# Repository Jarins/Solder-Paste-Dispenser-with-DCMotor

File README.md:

# 3D Printed Solder-Paste-Dispenser with DC motor
Motorized automatic solder paste dispenser. Easily printable on a 3D printer at home
+ **Thanks [kevarek](https://hackaday.io/Kevarek) for inspiration from this [project:](https://hackaday.io/project/169748-low-cost-solder-paste-dispenser)**
+ The idea came from this project, including some parts of the source code that were partially or completely reworked and many new ones added. 

## __Work-in-progress__ Latest version 2.21.11.3010

### Some differences:

+ Controled with 32bit processor STM32F103C8T6 ( original is STM32F030)
+ used output H-bridge for motor control [TB67H451FNG](https://www.aliexpress.com/item/1005001738294266.html?spm=a2g0s.9042311.0.0.27424c4dVMVyey). **No need cooling with during operation**.
+ 

+ [DC micromotor 6V / 60 rpm](https://www.aliexpress.com/item/33022320164.html?spm=a2g0s.9042311.0.0.266b4c4dmW3uVV) with gearbox without thread rod 

+ [Coupler](https://www.aliexpress.com/item/1005002015620915.html?spm=a2g0s.9042311.0.0.266b4c4dmW3uVV) 3/4mm to thread rod M4.

+ larger [syringe 10 ccm](https://www.aliexpress.com/item/10000092421369.html?spm=a2g0s.9042311.0.0.27424c4dw27aah)

+ **redesigned mechanism of operation and piston mounting and mainly redesigned Syringe mount, which can be removed and put on without disassembling the dispenser**

!! warning component links may be invalid over time !!

----------------------------------------------------------------------

+ [I2C OLED display 128x32](https://www.aliexpress.com/item/32879702750.html?spm=a2g0s.9042311.0.0.27424c4d1LUqwi) pixels for setting dispensing parameters and monitoring operating data
+ The supply voltage is 9V
+ The MicroUSB port is only used for 5V power supply when programming and debugging firmware to save battery. In this mode it is necessary to disconnect the 9V battery. The USB DM and DP pins are connected to the CPU, but the firmware does not respond to them. 
+ **Resistor R2** (in schematic) for measuring motor current is in the current version mounted with the value 0R, because the possibility of measuring this current is not used at the moment. When this value (0R) is used, the H-bridge turns off motor current monitoring.

#### PCB is designed by KiCAD software

+ Source code of Firmware is optimized for STM32CubeIDE and CubeMX software from ST Microelectronics.

+ Source code are easy aplicable to another IDE.

+ It would be a little more difficult to migrate to the Arduino IDE, but even that is partially possible - it has not been tested

+ CAD files are designed in SolidWorks, preview [here](https://grabcad.com/library/3d-printed-solder-paste-dispenser-1):

**Auto Extrusion cycle:**
+ PUSH button short switch ON -> Return from retract(retract duration time) -> Pulse for extrusion(pulse time) -> Retract(retract duration time)

**Manual Extrusion** 
+ PUSH button long switch ON(more as Retract duration time + Pulse time) -> extrusion until the PUSH button is switch OFF. This mode is used to insert a filled Syringe.

**Manual Retract**
+ PULL button switch ON -> retraction until the PULL button is switch OFF. This mode is using for remove and fill Syringe.
+
+ After selection, all parameters are immediately saved in the emulated EPROM (FLASH CPU).
+ Speed: 5, 10, 15 ...... 100% step by 5% 
+ Retract duration: 0(dissable), 100, 200 ...... 2500ms step by 100 milliseconds
+ Pulse after piston returned from retraction: 0(dissable), 100, 200 ..... 1500ms  step by 100 milliseconds 
+ Continuous measurement of battery voltage and CPU temperature
+ The firmware uses a non-blocking I2C DMA routine for the OLED display (this saves about 20 ms in the loop) **and Loop() no waiting to DMA complete as is usual in many of the examples given, which then makes the DMA a blocking wait routine**
+ In addition, non-blocking User Timers derived from SysTick interrupts are used, which do not stop the CPU while waiting for the Timer to run out. The number of these Timers is limited only by the CPU speed and the amount of allocated RAM) *more about this in* [*loop.c*](Software/CubeMX/Application/loop.c)

+ **Tasks**
+ [x] ***The continuation of the work consists in the completion of the control button mounted on the Syringe tube and the tuning of the SW for optimal paste dispensing. This is a game with engine on and off times and duty cycle of PWM wave***
+ [ ] Create a video with instructions for assembly and demonstration at work. Soon.
+ [ ] electronics attachment and power supply solution for the future possibility of 12V power supply from a 3D printer.
+ [ ] Next step is using this solder paste dispenser with a 3D printer. It may be necessary to use a stepping motor for dispensing instead. It has a better and more accurate dispensing control option. I have already finished the PCB for this variant with the DRV8825 controller and the NEMA14 stepper motor. 

UPDATE 11/22/2021:
- Syringe control button completed
- New version firmware 2.0. No blocked Dealy() in Loop() cycle

#### [Video Assembly and first testing](https://youtu.be/biS96wBTfaU) (redirect to YouTube) 
+ The first version of the printouts on my 3D printer

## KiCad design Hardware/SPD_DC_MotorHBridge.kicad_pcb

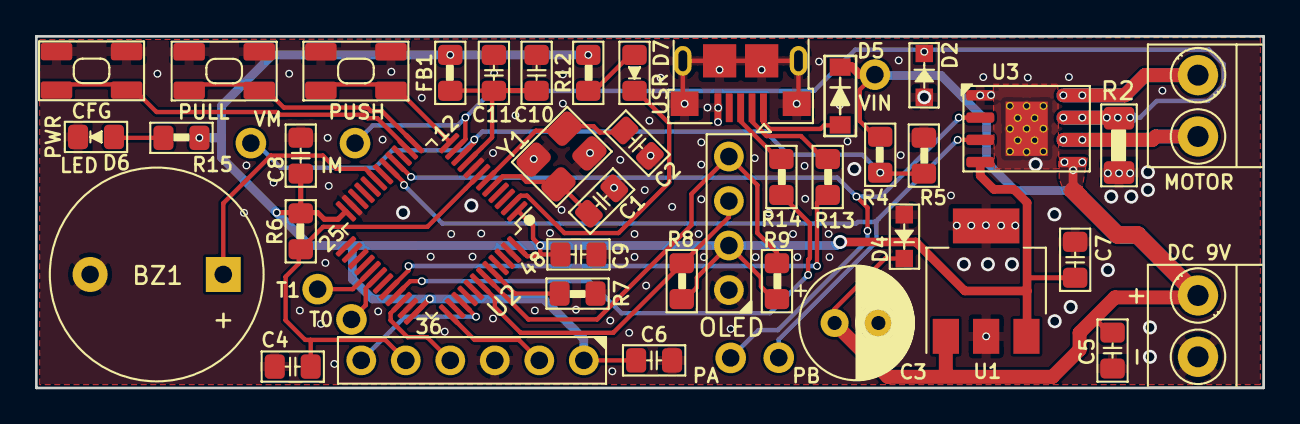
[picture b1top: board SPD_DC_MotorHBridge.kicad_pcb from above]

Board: 2 copper layers, 70.0 x 20.1 mm, 48 parts (0 on the bottom side), 33 nets.

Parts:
BZ1: Buzzer; Buzzer_12x9.5RM7.6
C1, C2: 10p; C_0805_2012Metric_Pad1.15x1.40mm_HandSolder
C3: 100u/35V; CP_Radial_D6.3mm_P2.50mm
C4, C6, C8, C9: 100n; C_0805_2012Metric_Pad1.15x1.40mm_HandSolder
C5: 1u; C_0805_2012Metric_Pad1.15x1.40mm_HandSolder
C7, C10: 2.2u; C_0805_2012Metric_Pad1.15x1.40mm_HandSolder
C11: 104; C_0805_2012Metric_Pad1.15x1.40mm_HandSolder
D2: 3.3V; D_SOD-323_HandSoldering
D4: 16V; D_SOD-323_HandSoldering
D5: MBR130LSFT1G; D_SOD-123
D6, D7: LED_Small_ALT; SMD_Dioda_0805
FB1: MPZ1608S221ATA00; R_0805_2012Metric_Pad1.15x1.40mm_HandSolder
IM1: MountingHole_Pad; Hole_Pad
J1, J2: Screw_Terminal_01x02; TerminalBlock_1x02_P3.50mm_Horizontal
J3: Display; PinHeader_1x04_P2.54mm_Vertical
J4: SWDIO; PinHeader_1x06_P2.54mm_Vertical
J5: USB_Micro; USB_Micro-B_Amphenol_10118193-0001LF_Horizontal
MP1, MP2, MP3: MountingHole_Pad; Hole_Pad
R2: 0; R_1206_3216Metric_Pad1.30x1.75mm_HandSolder
R4: 51k; R_0805_2012Metric_Pad1.15x1.40mm_HandSolder
R5: 5k6; R_0805_2012Metric_Pad1.15x1.40mm_HandSolder
R6, R7: 10k; R_0805_2012Metric_Pad1.15x1.40mm_HandSolder
R8, R9: 2k2; R_0805_2012Metric_Pad1.15x1.40mm_HandSolder
R12, R15: 510R; R_0805_2012Metric_Pad1.15x1.40mm_HandSolder
R13, R14: 22; R_0805_2012Metric_Pad1.15x1.40mm_HandSolder
SW1, SW2, SW3: TactSwichWhite; KEY-SMD-4.2X3.2X2.5-White
T0, T1: MountingHole_Pad; Hole_Pad
U1: MCP1826S-3.3; SOT-223-3_TabPin2
U2: STM32F103C8Tx; LQFP-48_7x7mm_P0.5mm
U3: TB67H451FNG; HSOP-8-1EP_3.9x4.9mm_P1.27mm_EP2.41x3.1mm_ThermalVias
VM1: MountingHole_Pad; Hole_Pad
Y1: TSX-3225 16MHz; Crystal_SMD_TSX3225-4Pin_3.2x2.5mm_HandSoldering

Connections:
+3V3: C6.1, C7.2, C8.1, C9.1, FB1.1, J3.2, J4.1, R6.1, R8.1, R9.1, R12.2, R15.1, U1.3, U2.1, U2.24, U2.36, U2.48, U3.4
+9V: C3.1, C5.2, D4.1, D5.1, J2.2, MP1.1, R4.1, U1.1, U3.5
/BCFG: SW3.1, SW3.2, U2.14
/BPULL: SW2.1, SW2.2, U2.13
/BPUSH: SW1.1, SW1.2, U2.12
/IM: D2.1, IM1.1, R2.1, U2.11, U3.7
/LED13: D7.1, U2.2
/MA: J1.2, U3.8
/MB: J1.1, U3.6
/NRST: C4.1, J4.5, R6.2, U2.7
/PA: MP2.1, U2.16, U3.2
/PB: MP3.1, U2.17, U3.3
/SCL: J3.3, R8.2, U2.42
/SDA: J3.4, R9.2, U2.43
/SWCLK: J4.2, U2.37
/SWDIO: J4.4, U2.34
/SWO: J4.6, U2.39
/USB_DM: R13.1, U2.32
/USB_DP: R14.1, U2.33
/VM: R4.2, R5.1, U2.10, VM1.1
GND: BZ1.2, C1.2, C2.2, C3.2, C4.2, C5.1, C6.2, C7.1, C8.2, C9.2, C10.1, C11.1, D2.2, D4.2, D6.1, J2.1, J3.1, J4.3, J5.5, J5.6, R2.2, R5.2, R7.2, SW1.3, SW1.4, SW2.3, SW2.4, SW3.3, SW3.4, U1.2, U2.8, U2.23, U2.35, U2.47, U3.1, Y1.2, Y1.4
unnamed: BZ1.1, U2.19
unnamed: C1.1, U2.5, Y1.1
unnamed: C2.1, U2.6, Y1.3
unnamed: C10.2, C11.2, FB1.2, U2.9
unnamed: D5.2, J5.1
unnamed: D6.2, R15.2
unnamed: D7.2, R12.1
unnamed: J5.2, R13.2
unnamed: J5.3, R14.2
unnamed: R7.1, U2.44
unnamed: T0.1, U2.30
unnamed: T1.1, U2.29

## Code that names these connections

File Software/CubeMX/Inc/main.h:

/* USER CODE BEGIN Header */
/**
  ******************************************************************************
  * @file           : main.h
  * @brief          : Header for main.c file.
  *                   This file contains the common defines of the application.
  ******************************************************************************
  * @attention
  *
  * <h2><center>&copy; Copyright (c) 2020 STMicroelectronics.
  * All rights reserved.</center></h2>
  *
  * This software component is licensed by ST under BSD 3-Clause license,
  * the "License"; You may not use this file except in compliance with the
  * License. You may obtain a copy of the License at:
  *                        opensource.org/licenses/BSD-3-Clause
  *
  ******************************************************************************
  */
/* USER CODE END Header */

/* Define to prevent recursive inclusion -------------------------------------*/
#ifndef __MAIN_H
#define __MAIN_H

#ifdef __cplusplus
extern "C" {
#endif

/* Includes ------------------------------------------------------------------*/
#include "stm32f1xx_hal.h"

/* Private includes ----------------------------------------------------------*/
/* USER CODE BEGIN Includes */

/* USER CODE END Includes */

/* Exported types ------------------------------------------------------------*/
/* USER CODE BEGIN ET */
typedef struct
{
	uint16_t Value;			// Time for Reload Timer in ms 0 = STOP
	uint16_t Tick;				// Counting Timer
	struct{
		uint8_t OverCount	:5;	// Count OverFlow
		uint8_t Reload		:1;	// Auto Reload
		uint8_t Over 		:1;	// OverFlow
		uint8_t Run 		:1;	// RunTimer
	}Control;
}TIMER;
/* USER CODE END ET */

/* Exported constants --------------------------------------------------------*/
/* USER CODE BEGIN EC */

/* USER CODE END EC */

/* Exported macro ------------------------------------------------------------*/
/* USER CODE BEGIN EM */

/* USER CODE END EM */

/* Exported functions prototypes ---------------------------------------------*/
void Error_Handler(void);

/* USER CODE BEGIN EFP */
void InitTimers(void);
void TimerAction(void);			/* pracuje s Timerem */
void ReadFromEprom(void);
void SaveToEprom(void);
void RestoreFromEprom(void);

//#define TRACE_SWO

#ifdef TRACE_SWO
uint16_t _write(uint16_t file, char *ptr, uint16_t len);
#endif

/* USER CODE END EFP */

/* Private defines -----------------------------------------------------------*/
#define LED_Pin GPIO_PIN_13
#define LED_GPIO_Port GPIOC
#define VM_Pin GPIO_PIN_0
#define VM_GPIO_Port GPIOA
#define IM_Pin GPIO_PIN_1
#define IM_GPIO_Port GPIOA
#define BPUSH_Pin GPIO_PIN_2
#define BPUSH_GPIO_Port GPIOA
#define BPUSH_EXTI_IRQn EXTI2_IRQn
#define BPULL_Pin GPIO_PIN_3
#define BPULL_GPIO_Port GPIOA
#define BPULL_EXTI_IRQn EXTI3_IRQn
#define BCFG_Pin GPIO_PIN_4
#define BCFG_GPIO_Port GPIOA
#define BCFG_EXTI_IRQn EXTI4_IRQn
#define SYSCLK_Pin GPIO_PIN_5
#define SYSCLK_GPIO_Port GPIOA
#define PB_Pin GPIO_PIN_6
#define PB_GPIO_Port GPIOA
#define PA_Pin GPIO_PIN_7
#define PA_GPIO_Port GPIOA
#define BEEP_Pin GPIO_PIN_1
#define BEEP_GPIO_Port GPIOB
#define TEST1_Pin GPIO_PIN_8
#define TEST1_GPIO_Port GPIOA
#define TEST_Pin GPIO_PIN_9
#define TEST_GPIO_Port GPIOA
#define SWDIO_Pin GPIO_PIN_13
#define SWDIO_GPIO_Port GPIOA
#define SWCLK_Pin GPIO_PIN_14
#define SWCLK_GPIO_Port GPIOA
#define SWO_Pin GPIO_PIN_3
#define SWO_GPIO_Port GPIOB
#define I2C_SCL_Pin GPIO_PIN_6
#define I2C_SCL_GPIO_Port GPIOB
#define I2C_SDA_Pin GPIO_PIN_7
#define I2C_SDA_GPIO_Port GPIOB
/* USER CODE BEGIN Private defines */

/* USER CODE END Private defines */

#ifdef __cplusplus
}
#endif

#endif /* __MAIN_H */

/************************ (C) COPYRIGHT STMicroelectronics *****END OF FILE****/

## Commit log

2021-11-09 Files
2021-11-10 Version 1.0
    Version 1.0
2021-11-10 Create SolderPasteMotor1.PNG
    Files
2021-11-11 PCB Library
2021-11-11 Rename Lib
2021-11-11 3DShapes
2021-11-11 rev.01
2021-11-22 Version 2.0
2021-11-29 ver 2.21.11.3010
    Last version firmware, added Pulse configuration
